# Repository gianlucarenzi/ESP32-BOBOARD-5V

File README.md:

# ESP32-BOBOARD-5V

**ESP32 NodeMCU 5V Tolerant Breakout Board per Monitoraggio Bus 6502**

## 🌐 Language / Lingua

---

## 📋 Indice

- [Panoramica del Progetto](#panoramica-del-progetto)
- [Caratteristiche Principali](#caratteristiche-principali)
- [Specifiche Tecniche](#specifiche-tecniche)
- [Visualizzazione 3D](#visualizzazione-3d)
- [Architettura Hardware](#architettura-hardware)
- [Firmware](#firmware)
- [Installazione e Setup](#installazione-e-setup)
- [Utilizzo](#utilizzo)
- [Diagrammi di Flusso](#diagrammi-di-flusso)
- [Tempistiche](#tempistiche)
- [File del Progetto](#file-del-progetto)
- [Produzione](#produzione)
- [Licenza](#licenza)
- [Contributi](#contributi)

## 🎯 Panoramica del Progetto

ESP32-BOBOARD-5V è una scheda breakout specializzata progettata per interfacciare un modulo ESP32 NodeMCU con sistemi basati su processore 6502, come l'Atari 8-bit. La scheda fornisce:

- **Tolleranza 5V** per tutti i pin GPIO
- **Monitoraggio del bus 6502** in tempo reale
- **Implementazione PBI (Parallel Bus Interface)** per Atari
- **Level shifting bidirezionale** per compatibilità 3.3V/5V
- **Connettori standard** per facile integrazione

### 🎮 Applicazioni Principali

- Monitoraggio e debug di sistemi 6502
- Implementazione di periferiche PBI per Atari
- Analisi del traffico del bus dati/indirizzi
- Espansione RAM a pagine da oltre 200 KB per Atari 130XE, finestra da 256 byte in $D500 (in stile GeoRAM)
- Espansione RAM 256 KB compatibile GeoRAM per Commodore 64, sulla porta di espansione (ambiente `c64`)
- Sviluppo di cartucce intelligenti

## ✨ Caratteristiche Principali

### Hardware
- **ESP32 NodeMCU** compatibile (240MHz dual-core)
- **3x TXS0108E** level shifters bidirezionali
- **Tolleranza 5V** su tutti i pin GPIO
- **Connettore USB-C** per programmazione e alimentazione
- **Connettore PBI** standard per Atari
- **Pin header** per accesso completo ai GPIO
- **LED di stato** e pulsanti di controllo

### Firmware
- **Espansione RAM a pagine da oltre 200 KB per Atari 130XE, in stile GeoRAM, senza ROM**: registri in $D100–$D1FF (`~D1XX`) e finestra RAM in $D500–$D5FF (`~CCTL`), decodificate dalla MMU/PLA dell'Atari; solo A0–A7 campionati
- **Ruoli fissi**: finestra RAM di 256 byte in $D500–$D5FF; registri in $D1xx: numero di banchi a $D1FB–$D1FC (sola lettura), registro del banco a 16 bit a $D1FD–$D1FE, latch di selezione PBI a $D1FF (bit 7, ID dispositivo `$80`); da non selezionato non pilota mai il bus
- **Banchi dall'heap**: all'avvio il firmware prende la DRAM libera dell'ESP32 in banchi da 256 byte (stima 200–230 KB, il valore esatto è stampato all'avvio)
- **Espansione RAM 256 KB compatibile GeoRAM per C64 (ambiente `c64`)**: la stessa scheda sulla porta di espansione: finestra RAM in IO1 $DE00–$DEFF, pagina in $DFFE e blocco da 16 KB in $DFFF (solo scrittura); /IO1 su J3 pin 12, /IO2 su J3 pin 11; 256 KB (16 blocchi, con ripiegamento degli indirizzi come una GeoRAM vera: circa 210 KB dalla DRAM e il resto dall'IRAM dell'ESP32)
- **Nessuna ROM, nessun MPD / EXTSEL**: tutti i pin del bus sono ingressi, D0–D7 diventano uscite solo per rispondere a una lettura
- **Dual-core**: Core 1 dedicato al bus (interrupt mascherati, decodifica durante PHI1), Core 0 stampa il log
- **Log lock-free** (Core 1 → Core 0): ogni accesso alle due pagine e ogni cambio di latch, con timestamp in microsecondi

## 🔧 Specifiche Tecniche

| Parametro | Valore |
|-----------|--------|
| **Microcontrollore** | ESP32-WROOM-32 |
| **Frequenza CPU** | 240 MHz (dual-core) |
| **Memoria Flash** | 4MB |
| **RAM** | 520KB |
| **GPIO disponibili** | 30 pin |
| **Level Shifters** | 3x TXS0108E (8-bit bidirezionali) |
| **Alimentazione** | 5V via USB-C o pin |
| **Logica I/O** | 3.3V/5V tolerant |
| **Dimensioni PCB** | 21.7mm x 21.7mm |
| **Layers** | 4 layer PCB |

### Pinout 6502 Bus

| Segnale | Pin ESP32 | Descrizione |
|---------|-----------|-------------|
| **D0-D7** | GPIO4, GPIO5, GPIO13, GPIO14, GPIO16, GPIO17, GPIO18, GPIO19 | Data Bus (Bidirezionale) |
| **A0-A3** | GPIO34, GPIO35, GPIO36, GPIO39 | Address Bus LSB (Input Only) |
| **A4-A7** | GPIO32, GPIO33, GPIO21, GPIO27 | Address Bus |
| **PHI2** | GPIO2 | Clock 6502 (1.79 MHz) |
| **R/W** | GPIO15 | Read/Write |
| **~D1XX** | GPIO22 | Pagina $D100–$D1FF, dalla MMU/PLA (Active Low, Input) |
| **~CCTL** | GPIO23 | Pagina $D500–$D5FF, dalla MMU/PLA (Active Low, Input) |
| **TX debug** | GPIO1 | Console seriale 115200 bps (anche su J4 pin 3) |

Non usati dal firmware: GPIO12 (ancora collegato a U1 / J3 pin 4, pin di strapping), GPIO25 e GPIO26 (canali TXS0108E liberi), GPIO0 e GPIO3 (non portati su J3).

## 🎨 Visualizzazione 3D

### 📱 Viewer Online Interattivi

Visualizza i modelli 3D direttamente nel browser:

### 📥 Download File 3D

| Formato | Descrizione | Download |
|---------|-------------|----------|
| **STEP** | Modello CAD parametrico |  |
| **WRL** | Modello VRML per rendering |  |

### 🖼️ Galleria Immagini 3D

<table>
  <tr>
    <td align="center">
      
      <br/><b>Vista Isometrica</b>
    </td>
    <td align="center">
      
      <br/><b>Vista Superiore</b>
    </td>
  </tr>
  <tr>
    <td align="center">
      
      <br/><b>Vista Inferiore</b>
    </td>
    <td align="center">
      
      <br/><b><a href="schematics/ESP32-BOBOARD-5V.pdf">📄 Schema Elettrico</a></b>
    </td>
  </tr>
</table>

### 🛠️ Software Consigliati per Visualizzazione

| Software | Formato | Piattaforma | Gratuito |
|----------|---------|-------------|----------|
| **FreeCAD** | STEP, WRL | Windows, Linux, macOS | ✅ |
| **Fusion 360** | STEP | Windows, macOS | ✅ (Personal) |
| **Blender** | WRL | Windows, Linux, macOS | ✅ |
| **MeshLab** | WRL | Windows, Linux, macOS | ✅ |
| **CAD Exchanger Viewer** | STEP, WRL | Browser | ✅ |
| **3D Viewer Online** | STEP, WRL | Browser | ✅ |
| **Autodesk Viewer** | STEP | Browser | ✅ |

---

## 🏗️ Architettura Hardware

### Schema a Blocchi

### Level Shifting

La scheda utilizza tre TXS0108E per garantire la compatibilità tra i livelli logici 3.3V dell'ESP32 e i 5V del sistema 6502.  I canali seguono i pin del modulo, non le funzioni:

- **U1**: PHI2 (GPIO2), D0 (GPIO4), D1 (GPIO5), GPIO12 (non usato), D2 (GPIO13), D3 (GPIO14), R/W (GPIO15), D6 (GPIO18)
- **U3**: D7 (GPIO19), A6 (GPIO21), ~D1XX (GPIO22), ~CCTL (GPIO23), GPIO25 e GPIO26 (liberi), A7 (GPIO27), A4 (GPIO32)
- **U4**: A5 (GPIO33), A0 (GPIO34), A1 (GPIO35), A2 (GPIO36), A3 (GPIO39), D4 (GPIO16), D5 (GPIO17); canale 8 libero

`TXS_EN` (OE di tutti e tre) è tenuto alto da R1/R3/R4; SW1 lo porta a GND per isolare l'ESP32 dal bus.

## 💻 Firmware

### Architettura Software

Il firmware è basato su FreeRTOS e utilizza entrambi i core dell'ESP32:

- **Core 0**: `LogTask`, unico scrittore sulla seriale
- **Core 1**: `MonitorTask` in IRAM, con interrupt mascherati e watchdog degli interrupt disattivato, possiede il bus 6502

### Funzionalità Principali

#### 1. Ciclo di bus

- **PHI1**: 200 ns dopo la discesa di PHI2 (`BUS_ADDR_SETTLE_NS`) campiona A0–A7, R/W, `~D1XX` e `~CCTL`; per una lettura della finestra RAM o di un registro ($D1FB–$D1FE) scrive il byte in `GPIO.out` con le uscite ancora spente
- **Salita di PHI2**: un solo store accende D0–D7; se la selezione compare solo sul fronte di salita, il byte viene pilotato in ritardo
- **Scrittura**: il dato è campionato 120 ns dopo la salita di PHI2 (`BUS_WR_SAMPLE_NS`)
- **Discesa di PHI2**: D0–D7 rilasciati; l'evento del ciclo va nel log durante la PHI1 successiva

#### 2. Atari 130XE: espansione RAM a pagine da oltre 200 KB (in stile GeoRAM)

Non è una GeoRAM (sull'Atari non è mai esistita) e non è compatibile con la memoria estesa del 130XE / RAMBO, quella commutata via PORTB in $4000–$7FFF: DOS con RAMdisk e programmi per la memoria estesa non la vedono, serve software scritto per questa mappa.  La quantità esatta (stima 200–230 KB) la stampa il banner all'avvio.

Ruoli fissi, come la GeoRAM del C64 fra IO2 e IO1: la pagina PBI $D1xx contiene i registri, la pagina CCTL $D500–$D5FF è una finestra di 256 byte sulla RAM.

| Indirizzo | Funzione | Note |
|-----------|----------|------|
| **$D500–$D5FF** | Finestra RAM: 256 byte del banco corrente (R/W) | Solo con il dispositivo selezionato |
| **$D1FB–$D1FC** | Numero di banchi (R, 16 bit) | Dipende dall'heap libero, scritture ignorate |
| **$D1FD–$D1FE** | Registro del banco (R/W, 16 bit, little-endian) | Un banco oltre il numero disponibile non risponde |
| **$D1FF** | Latch di selezione PBI (W: bit 7 = ID `$80`) | Mai pilotato in lettura ($D1FF è lo stato IRQ PBI) |
| **$D100–$D1FA** | Riservato | Mai pilotato, scritture ignorate |

Regole PBI: una scrittura in $D1FF seleziona il dispositivo con il bit 7 a 1 e lo deseleziona con il bit 7 a 0 (ogni dispositivo PBI guarda solo il proprio bit).  Da non selezionato non pilota mai il bus e ignora ogni scrittura tranne il latch.

Collegamento all'Atari 130XE (slot cartuccia ed ECI).  Sull'800XL il connettore PBI non porta `~D1XX`: $D1xx va decodificato da A8–A15 con logica esterna, non prevista su questa scheda:

Vista breadboard, stile Fritzing:

I banchi da 256 byte vengono allocati all'avvio dall'heap DRAM libero dell'ESP32 (meno 24 KB di riserva per il sistema).  Indirizzo lineare: banco = indirizzo >> 8, offset = indirizzo & $FF.  All'accensione: non selezionato, banco 0, RAM a `$00`; il dispositivo non vede il RESET dell'Atari e mantiene lo stato, la RAM non si conserva al reset dell'ESP32.  Senza ROM la scansione PBI dell'OS non trova la firma a $D803 / $D80B e salta il dispositivo: i programmi lo selezionano direttamente scrivendo `$80` in $D1FF; la scansione scrive `$80` e poi `$00` in $D1FF, quindi il dispositivo resta deselezionato.

#### 3. Commodore 64: espansione RAM 256 KB compatibile GeoRAM (ambiente `c64`)

La stessa scheda, con l'ambiente `c64` (`-D BUS_C64=1`), diventa un'espansione RAM compatibile GeoRAM (stessi registri $DE00, $DFFE, $DFFF) per la porta di espansione del C64, con lo stesso schema del firmware di Vera-Module-RBL-C64.  "geoRAM" era un prodotto di Berkeley Softworks, solo nel taglio da 512 KB: questa è un'espansione compatibile da 256 KB, da confermare con il banner all'avvio.

| Indirizzo | Funzione | Note |
|-----------|----------|------|
| **$DE00–$DEFF** (/IO1) | Finestra di 256 byte sulla RAM | Lettura e scrittura |
| **$DFFE** (/IO2) | Pagina nel blocco (0–63) | Solo scrittura, in lettura non pilotato |
| **$DFFF** (/IO2) | Blocco da 16 KB (0–15) | Solo scrittura, in lettura non pilotato |

- **Sempre attiva**, senza latch, come la cartuccia originale; il resto di IO2 non è decodificato (nessun mirror in $DF80–$DFFD)
- **256 KB, 16 blocchi**: indirizzo = blocco × 16384 + pagina × 256 + offset; il blocco è limitato alla dimensione (il blocco 16 coincide con lo 0) come su una GeoRAM vera, così la rilevazione della dimensione vede una 256 KB.  `-D GEORAM_KB=...` per un'altra potenza di 2
- **Memoria**: circa 210 KB dalla DRAM dell'ESP32 e il resto dall'IRAM libera, letta e scritta solo a 32 bit; se non basta, il firmware scende a 128 KB e lo dice nel banner.  La geoRAM originale era da 512 KB: il software che pretende quel taglio non funziona
- **Ciclo di bus**: il VIC-II possiede il bus durante PHI1, quindi tutto avviene con PHI2 alto: dopo la salita il firmware attende /IO1 o /IO2 per al massimo 200 ns (`IO_QUALIFY_NS`), legge A0–A7 e, in lettura, pilota subito il byte fino alla discesa di PHI2; in scrittura il dato è campionato 300 ns dopo la salita (`BUS_WR_SAMPLE_NS`)
- **Stato**: azzerato all'accensione, mantenuto al reset del C64; la RAM non si conserva al reset dell'ESP32

Collegamento alla porta di espansione (pinout del C64 verificato su c64-wiki.com e retroisle.com):

Vista breadboard, stile Fritzing:

| Segnale | Porta C64 | J3 |
|---------|-----------|----|
| **/IO1** | 7 | 12 (GPIO23, ingresso `~CCTL`) |
| **/IO2** | 10 | 11 (GPIO22, ingresso `~D1XX`) |
| D0 / D1 / D2 / D3 | 21 / 20 / 19 / 18 | 2 / 3 / 5 / 6 |
| D4 / D5 / D6 / D7 | 17 / 16 / 15 / 14 | 22 / 23 / 8 / 9 |
| A0 / A1 / A2 / A3 | Y / X / W / V | 18 / 19 / 20 / 21 |
| A4 / A5 / A6 / A7 | U / T / S / R | 16 / 17 / 10 / 15 |
| Φ2 | E | 1 |
| R/W | 5 | 7 |
| GND | 1, 22, A, Z | 29, 30 |
| +5V | 2, 3 | 31, 32 |

Output seriale (i numeri di pagine e di memoria libera dipendono dalla scheda):

```
[6502_monitor] GeoRAM on the C64 expansion port: 256 KB = 16 blocks x 16 KB
[6502_monitor] Pages: <d> in DRAM, <i> in IRAM, <b> heap blocks; left <h> bytes DRAM, <r> bytes IRAM
[6502_monitor] IO1 $DE00-$DEFF RAM, IO2 $DFFE page, $DFFF block (write-only)
[6502_monitor] /IO1 on J3 pin 12 (GPIO23), /IO2 on J3 pin 11 (GPIO22)
[6502_monitor] Bus loop on Core 1 (/IOx within 200 ns, write sample 300 ns after PHI2 rises), log 115200 baud
[    2.000000] [DFFF - GEORAM_BLOCK        ] W $04  SEL
[    2.000010] [DFFE - GEORAM_PAGE         ] W $23  SEL
[    2.000020] [DE45 - RAM blk $04 pg $23 +$45] R $12  SEL DRV
```

Uso dal C64:
```
LDA #$04 : STA $DFFF   ; blocco 4
LDA #$23 : STA $DFFE   ; pagina 35
LDA $DE45              ; byte GeoRAM $12345
```

Da verificare sull'hardware: il banner (256 KB effettivi), le temporizzazioni all'oscilloscopio e la compatibilità con GEOS e il software GeoRAM.

## 🚀 Installazione e Setup

### Requisiti Hardware
- ESP32 NodeMCU DevKit V1 (30 pin, ESP32-WROOM-32)
- Cavo USB-C per programmazione
- Sistema 6502 target (es. Atari 130XE)
- Connessioni bus secondo pinout

### Requisiti Software
- [PlatformIO](https://platformio.org/) o Arduino IDE
- ESP32 Arduino Core v2.0.14
- Driver USB-C per il sistema operativo

### Compilazione Firmware

1. **Clone del repository**:
```bash
git clone https://github.com/gianlucarenzi/esp32-boboard-5v.git
cd ESP32-BOBOARD-5V/firmware/6502_monitor
```

2. **Configurazione PlatformIO** (estratto di `platformio.ini`):
```ini
[env]
extra_scripts = post:efuse_vdd_sdio.py
monitor_rts = 0
monitor_dtr = 0
custom_efuse_vdd_sdio = 3.3V

[env:nodemcu-32s]
platform = espressif32@6.6.0
board = nodemcu-32s
framework = arduino
monitor_speed = 115200
upload_speed = 921600
board_build.f_cpu = 240000000

[env:c64]                      ; Commodore 64, GeoRAM
extends = env:nodemcu-32s
build_flags = ${env:nodemcu-32s.build_flags} -D BUS_C64=1
```

Il modulo si programma **sempre scollegato dall'Atari o dal C64**, collegato solo al PC.  Prima di ogni upload `efuse_vdd_sdio.py` verifica gli efuse VDD_SDIO e, se sono vergini, li programma a 3,3 V (**irreversibile**), così GPIO12 non viene più letto al reset.

3. **Compilazione e upload**:
```bash
pio run -e nodemcu-32s --target upload   # Atari
pio run -e c64 --target upload           # Commodore 64 (GeoRAM)
pio device monitor
```

### Configurazione Hardware

1. **Connessione ESP32**: Inserire il modulo NodeMCU nei socket
2. **Alimentazione**: Collegare USB-C o alimentazione 5V
3. **Bus 6502**: Collegare secondo il pinout specificato
4. **Test**: Eseguire modalità test per verifica connessioni

## 📊 Utilizzo

### Avvio Sistema

1. **Power-on**: Alimentare la scheda
2. **Monitor seriale**: Aprire terminale a 115200 baud
3. **Inizializzazione**: Attendere messaggio di ready
4. **Connessione 6502**: Collegare al sistema target

### Output Seriale

Il firmware stampa su Core 0 ogni evento registrato da Core 1 in un ring buffer lock-free.
Il formato è `[secondi.microsecondi]`:

```
[6502_monitor] Banked RAM PBI / CCTL peripheral, device ID $80
[6502_monitor] <n> banks x 256 bytes = <k> KB, <b> heap blocks, <h> bytes of heap left
[6502_monitor] RAM window $D500-$D5FF; count $D1FB-$D1FC, bank $D1FD-$D1FE, select $D1FF
[6502_monitor] Bus loop on Core 1 (settle 200 ns, write sample 120 ns), log 115200 baud
[    1.234567] [D1FF - PBI_SELECT          ] W $80  SELECTED
[    1.234601] [D1FD - BANK_SELECT_L       ] W $03  SEL
[    1.234620] [D1FE - BANK_SELECT_H       ] W $01  SEL
[    1.234640] [D505 - RAM bank $0103 +$05 ] W $AA  SEL
[    1.234680] [D505 - RAM bank $0103 +$05 ] R $AA  SEL DRV
[    1.300000] [D105 - RESERVED            ] R $FF  SEL
```

- `PBI_SELECT` — scrittura del latch e nuovo stato: `SELECTED` / `DESELECTED`
- `SEL` = dispositivo selezionato, `DRV` = byte pilotato dal dispositivo, `-` = non selezionato (il byte è quello presente sul bus)
- Gli offset sono mostrati come `RAM bank $bbbb +$oo`, `BANK_COUNT_L/H`, `BANK_SELECT_L/H`, `PBI_SELECT` o `RESERVED`; i numeri di banchi nell'esempio sono indicativi
- Il timestamp viene dal contatore di cicli del Core 1 (CCOUNT esteso a 64 bit)
- Ogni riga è una sola `Serial.write()`: le righe non si mescolano mai; gli eventi persi quando il ring è pieno vengono contati
- Debug in sola lettura anche su J4: GND (pin 1) e TX0 (pin 3, 3,3 V); RX0 (pin 2) va lasciato scollegato

## 📈 Diagrammi di Flusso

### Flusso Principale del Monitor

### Protocollo di Selezione (PBI)

## ⏱️ Tempistiche

### Timing Critici

| Operazione | Tempo | Note |
|------------|-------|------|
| **PHI2 Period** | 1.77 MHz (PAL) / 1.79 MHz (NTSC) | Clock Atari 6502 |
| **Address Setup** | <100ns | Prima del rising edge PHI2 |
| **Data Setup** | <200ns | Per operazioni di write |
| **Data Hold** | <100ns | Dopo falling edge PHI2 |
| **GPIO Read** | ~125ns | Lettura registri ESP32 |
| **Level Shift** | <10ns | Propagazione TXS0108E |

### Diagramma Temporale Bus 6502

Ciclo di bus Atari visto dal firmware `nodemcu-32s` (ns dalla discesa di PHI2; generato da [`docs/timing.py`](firmware/6502_monitor/docs/timing.py)):

### Performance del Monitor

- **Campionamento**: un ciclo di bus per volta, Core 1 dedicato al 100%
- **Risposta in lettura**: byte (RAM del banco o registro) preparato durante PHI1, uscite accese subito dopo la salita di PHI2 (da misurare all'oscilloscopio)
- **Throughput seriale**: 115200 baud per debug (`LOG_BAUD`)
- **Compatibilità**: Atari PAL (1.77 MHz) e NTSC (1.79 MHz)

## 📁 File del Progetto

### Struttura Directory

```
ESP32-BOBOARD-5V/
├── 📁 firmware/
│   └── 📁 6502_monitor/
│       ├── 📄 platformio.ini          # Configurazione PlatformIO (ambienti nodemcu-32s / Atari e c64 / C64)
│       ├── 📄 efuse_vdd_sdio.py       # Controllo/programmazione efuse VDD_SDIO prima di ogni upload
│       ├── 📁 src/
│       │   └── 📄 main.cpp            # Firmware ESP32 (RAM a banchi PBI/CCTL + monitor)
│       ├── 📄 README.md, HARDWARE.md, PIN_MAPPING.md/.tex/.pdf, Logs.md
├── 📁 schematics/
│   └── 📄 ESP32-BOBOARD-5V.pdf    # Schema elettrico
├── 📁 3D/
│   ├── 🖼️ ESP32-BOBOARD-5V.png    # Render 3D
│   ├── 🖼️ ESP32-BOBOARD-5V_TOP.png
│   └── 🖼️ ESP32-BOBOARD-5V_BOTTOM.png
├── 📁 images/
│   ├── 📄 ESP32-BOBOARD-5V.step   # Modello 3D (output_job.sh)
│   └── 📄 ESP32-BOBOARD-5V.wrl    # Modello VRML (output_job.sh)
├── 📁 production/
│   ├── 📄 *.gbl, *.gtl           # File Gerber
│   ├── 📄 *.drl                  # File drill
│   └── 📄 ESP32BOBOARD-5V-1.0.zip
├── 📁 ibom/
│   └── 📄 ibom.html              # Interactive BOM
├── 📄 ESP32-BOBOARD-5V.kicad_pcb  # PCB KiCad
├── 📄 ESP32-BOBOARD-5V.sch        # Schema KiCad
├── 📄 ESP32-BOBOARD-5V.csv        # Bill of Materials
└── 📄 README.md                   # Questo file
```

### File di Produzione

#### Bill of Materials (BOM)

| Componente | Quantità | Package | LCSC Part |
|------------|----------|---------|-----------|
| **TXS0108EPW** | 3 | TSSOP-20 | C17206 |
| **100µF Capacitor** | 9 | 0805 | C141660 |
| **100nF Capacitor** | 1 | 0805 | C840116 |
| **10kΩ Resistor** | 4 | 0805 | C84376 |
| **5.1kΩ Resistor** | 2 | 0805 | C27834 |
| **1% Precision Resistor** | 2 | 0805 | C328378 |
| **Pin Socket 1x15** | 2 | THT | - |
| **Pin Header 2x16** | 1 | SMD | C6332241 |
| **USB-C Connector** | 1 | SMD | C3197885 |
| **SPST Switch** | 1 | SMD | C319052 |

#### File Gerber
- **4-layer PCB** ottimizzato per segnali ad alta velocità
- **Impedenza controllata** per linee critiche
- **Ground planes** per riduzione EMI
- **Via stitching** per integrità del segnale

## 🏭 Produzione

### Specifiche PCB

| Parametro | Valore |
|-----------|--------|
| **Layers** | 4 |
| **Thickness** | 1.6mm |
| **Min Track** | 0.1mm |
| **Min Via** | 0.2mm |
| **Copper Weight** | 1oz (35μm) |
| **Surface Finish** | HASL Lead-Free |
| **Solder Mask** | Green |
| **Silkscreen** | White |

### Assembly

1. **SMD Components**: Assemblaggio automatico raccomandato
2. **THT Components**: Saldatura manuale pin headers
3. **Test**: Verifica continuità e test funzionale
4. **Programming**: Upload firmware di test

## 📜 Licenza

Questo progetto è rilasciato sotto **GNU General Public License v3.0**.

```
ESP32-BOBOARD-5V - ESP32 NodeMCU 5V Tolerant Breakout Board
Copyright (C) 2024 RetroBitLab

This program is free software: you can redistribute it and/or modify
it under the terms of the GNU General Public License as published by
the Free Software Foundation, either version 3 of the License, or
(at your option) any later version.
```

Vedi il file [LICENSE](LICENSE) per i dettagli completi.

## 🤝 Contributi

I contributi sono benvenuti! Per contribuire:

1. **Fork** del repository
2. **Crea** un branch per la tua feature (`git checkout -b feature/AmazingFeature`)
3. **Commit** delle modifiche (`git commit -m 'Add some AmazingFeature'`)
4. **Push** al branch (`git push origin feature/AmazingFeature`)
5. **Apri** una Pull Request

### Aree di Contributo

- 🐛 **Bug fixes** e miglioramenti firmware
- 📚 **Documentazione** e tutorial
- 🔧 **Hardware** ottimizzazioni e varianti
- 🧪 **Testing** e validazione
- 🎨 **Examples** e progetti dimostrativi

### Reporting Issues

Per segnalare problemi, utilizzare il sistema di [Issues](../../issues) includendo:
- Descrizione dettagliata del problema
- Versione hardware e firmware
- Log seriali se disponibili
- Passi per riprodurre il problema

---

## 📞 Contatti

- **Progetto**: ESP32-BOBOARD-5V
- **Autore**: RetroBitLab
Repository: [GitHub](https://github.com/gianlucarenzi/esp32-boboard-5v)
- **Documentazione**: [Wiki](../../wiki)

---

*Realizzato con ❤️ per la comunità retro-computing*

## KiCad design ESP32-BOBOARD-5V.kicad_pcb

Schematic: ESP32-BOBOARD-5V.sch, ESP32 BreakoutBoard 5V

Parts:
C1, C2, C3, C4, C5, C6, C7, C8, C9: 100uF; C_0805_2012Metric_Pad1.18x1.45mm_HandSolder; LCSC C141660
C10: 100nF; C_0805_2012Metric_Pad1.18x1.45mm_HandSolder; LCSC C840116
GR1: LOGO; KiCad-Logo2_5mm_SilkScreen
GR2: LOGO; ESP32_BOBOARD_5V_21.7mmx21.7mm
J1, J2: Conn_01x15; PinSocket_1x15_P2.54mm_Vertical
J3: CONN_02x16_PIN_SMD_Odd_Even_2.54mm; PinHeader_2x16_P2.54mm_Vertical_SMD; LCSC C6332241
J4: Conn_01x03_Male; PinHeader_1x03_P2.54mm_Vertical_SMD_Pin1Left; LCSC C41417360
J5: DX07S016JA1R1500; JAE_DX07S016JA1R1500; PARTREV 1; LCSC C3197885
R1, R2, R3, R4: 10K; R_0805_2012Metric_Pad1.20x1.40mm_HandSolder; LCSC C84376
R5, R6: 5K1; R_0805_2012Metric_Pad1.20x1.40mm_HandSolder; LCSC C27834
R7, R8: CREZ08051%; R_0805_2012Metric_Pad1.20x1.40mm_HandSolder; LCSC C328378
SW1: SPST_SWITCH_SMD_4P,4.1x5.4mm; SW_DIP_SPSTx02_DSHP02TS-S; LCSC C319052
U1, U3, U4: TXS0108EPW; TSSOP-20_4.4x6.5mm_P0.65mm; LCSC C17206

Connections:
+3V3: C1.1, C4.1, C6.1, C8.1, J1.1, J3.27, J3.28, R1.2, R2.2, R3.2, R4.2, U1.2 (VCCA), U3.2 (VCCA), U4.2 (VCCA)
+5V: C2.1, C3.1, C5.1, C7.1, C9.1, J2.1, J3.31, J3.32, J5.2 (VBUS), J5.11 (VBUS), U1.19 (VCCB), U3.19 (VCCB), U4.19 (VCCB)
/D2: J1.4, U1.1 (A1)
/D4: J1.5, U1.3 (A2)
/D5: J1.8, U1.4 (A3)
/D12: J2.4, U1.5 (A4)
/D13: J2.3, U1.6 (A5)
/D14: J2.5, U1.7 (A6)
/D15: J1.3, U1.8 (A7)
/D18: J1.9, U1.9 (A8)
/D19: J1.10, U3.1 (A1)
/D21: J1.11, U3.3 (A2)
/D22: J1.14, U3.4 (A3)
/D23: J1.15, U3.5 (A4)
/D25: J2.8, U3.6 (A5)
/D26: J2.7, U3.7 (A6)
/D27: J2.6, U3.8 (A7)
/D32: J2.10, U3.9 (A8)
/D33: J2.9, U4.1 (A1)
/D34: J2.12, U4.3 (A2)
/D35: J2.11, U4.4 (A3)
/EN: J2.15, J3.26, R2.1
/RX0: J1.12, J4.2
/RX2: J1.6, U4.7 (A6)
/TX0: J1.13, J4.3
/TX2: J1.7, U4.8 (A7)
/USBD_N: J5.5 (D-), J5.8 (D-), R7.1
/USBD_P: J5.6 (D+), J5.7 (D+), R8.1
/VN: J2.13, U4.6 (A5)
/VP: J2.14, U4.5 (A4)
/mD2: J3.1, U1.20 (B1)
/mD4: J3.2, U1.18 (B2)
/mD5: J3.3, U1.17 (B3)
/mD12: J3.4, U1.16 (B4)
/mD13: J3.5, U1.15 (B5)
/mD14: J3.6, U1.14 (B6)
/mD15: J3.7, U1.13 (B7)
/mD18: J3.8, U1.12 (B8)
/mD19: J3.9, U3.20 (B1)
/mD21: J3.10, U3.18 (B2)
/mD22: J3.11, U3.17 (B3)
/mD23: J3.12, U3.16 (B4)
/mD25: J3.13, U3.15 (B5)
/mD26: J3.14, U3.14 (B6)
/mD27: J3.15, U3.13 (B7)
/mD32: J3.16, U3.12 (B8)
/mD33: J3.17, U4.20 (B1)
/mD34: J3.18, U4.18 (B2)
/mD35: J3.19, U4.17 (B3)
/mRX2: J3.22, U4.14 (B6)
/mTX2: J3.23, U4.13 (B7)
/mVN: J3.21, U4.15 (B5)
/mVP: J3.20, U4.16 (B4)
GND: C1.2, C2.2, C3.2, C4.2, C5.2, C6.2, C7.2, C8.2, C9.2, C10.2, J1.2, J2.2, J3.29, J3.30, J4.1, J5.1 (GND), J5.12 (GND), R5.2, R6.1, SW1.2, U1.11 (GND), U3.11 (GND), U4.11 (GND)
unnamed: C10.1, J5.S1 (SHIELD), J5.S2 (SHIELD), J5.S3 (SHIELD), J5.S4 (SHIELD), J5.S5 (SHIELD), J5.S6 (SHIELD)
unnamed: J5.3 (CC1), R5.1
unnamed: J5.9 (CC2), R6.2
TXS_EN: R1.1, R3.1, R4.1, SW1.3, U1.10 (OE), U3.10 (OE), U4.10 (OE)

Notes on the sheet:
Yellow
Orange
Black
DEBUG UART TX0/RX0
ESP32 MODULE STRIP
LEVEL SHIFTERS
5V TOLERANT HEADER CONNECTOR
USB-C POWER
Do not connect USB ESP32 __and__ USB J5 at the same time!
Normal Mode OFF-OFF When PROGRAMMING ESP32 ON-ON

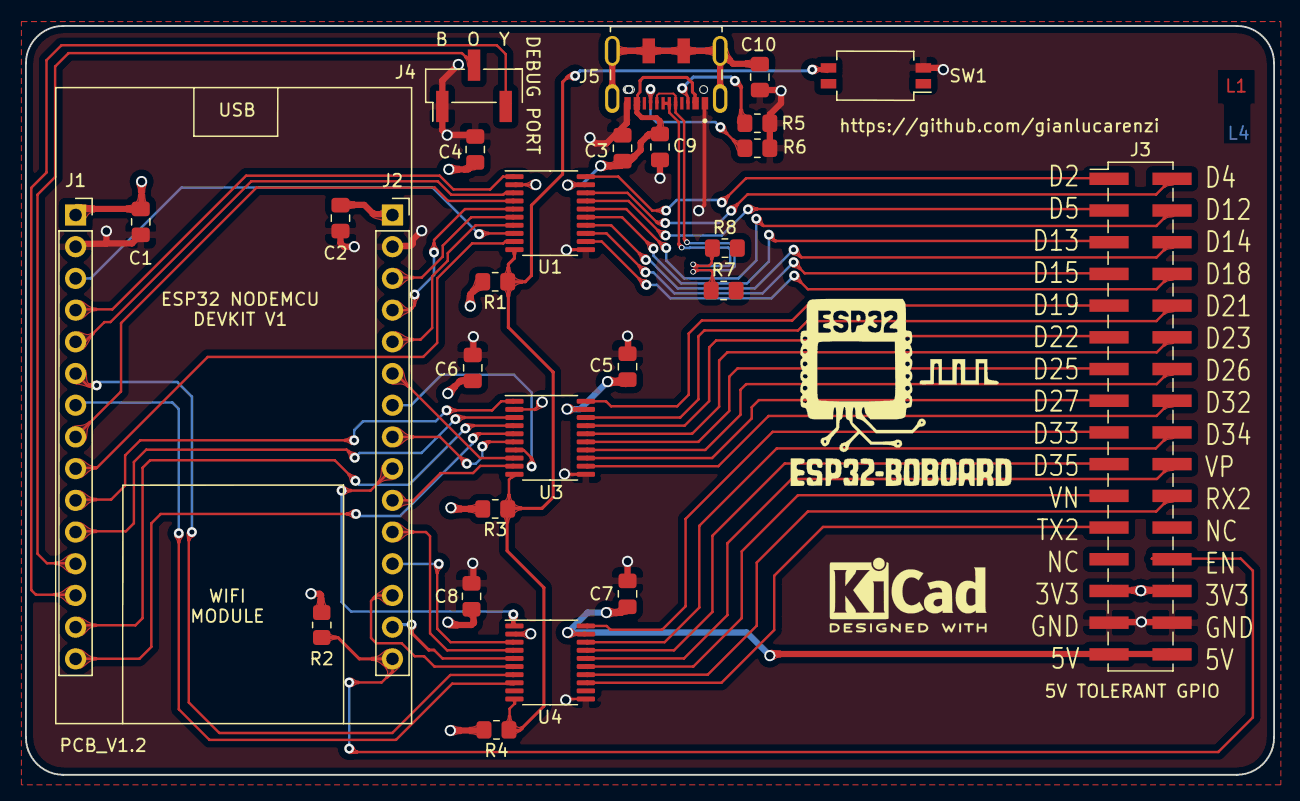
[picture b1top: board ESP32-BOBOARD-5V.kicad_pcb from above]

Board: 4 copper layers, 100.0 x 60.0 mm, 29 parts (0 on the bottom side), 58 nets.

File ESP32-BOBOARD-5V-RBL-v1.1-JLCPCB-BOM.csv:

Comment,Designator,Footprint,LCSC
100nF,C10,Capacitor_SMD:C_1210_3225Metric_Pad1.33x2.70mm_HandSolder,C2351189
100uF,"C1,C2,C3,C4,C5,C6,C7,C8,C9",Capacitor_SMD:C_1210_3225Metric_Pad1.33x2.70mm_HandSolder,C90143
Conn_02x16_Counter_Clockwise,J3,Connector_PinHeader_2.54mm:PinHeader_2x16_P2.54mm_Vertical_SMD,C3294474 
Conn_01x03_Male,J4,Connector_PinHeader_2.54mm:PinHeader_1x03_P2.54mm_Vertical_SMD_Pin1Left,C41417360
DX07S016JA1R1500,J5,RetroBitLab:JAE_DX07S016JA1R1500,C3197885
10K,"R1,R2,R3,R4",Resistor_SMD:R_1210_3225Metric_Pad1.30x2.65mm_HandSolder,C620660
5K1,"R5,R6",Resistor_SMD:R_1210_3225Metric_Pad1.30x2.65mm_HandSolder,C2119494
CREZ12101%,"R7,R8",Resistor_SMD:R_1210_3225Metric_Pad1.30x2.65mm_HandSolder,C2974058
"SPST_SWITCH_SMD_4P,4.1x5.4mm",SW1,RetroBitLab:SW_DIP_SPSTx02_DSHP02TS-S,C319052
TXS0108EPW,"U1,U3,U4",Package_SO:TSSOP-20_4.4x6.5mm_P0.65mm,C17206

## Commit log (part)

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2025-07-23 Added via UPLOAD
2025-07-23 Sent to JLCPCB 23 Jul 2025 PCB V1.0
2025-07-23 First plot
2025-07-23 First build
2025-07-23 First 3D
2025-07-23 Updated with area-fills and other silkscreen information
2025-07-31 First commit. Compile in a shell
2025-07-31 Settings for UART
2025-07-31 First commit.
2025-07-31 GPIO Manual Test
2025-07-31 AUTO TEST (Shorting IN <--> OUT)
2025-07-31 Normal mode by default
2025-07-31 Aggiornato commento. Attenzione: il pin 36 non viene testato
2025-08-01 Not useful. Must be in the .gitignore
2025-08-01 Added the dip-switch for programming
2025-08-01 Added the dip-switch for programming Added the ESP32 BOBOARD LOGO
2025-08-01 The Montor code is now on CPU Core 1 (it's seems to be quicker than Core 0) Core 0 is now running SerialTask
2025-09-12 Template/Placeholder
2025-09-15 Updated to a better execution timeslice
2025-09-19 Added to project. Must be checked first!
2025-09-19 Updated to reflect new components from library and LCSC availability
2025-09-19 Added
2025-09-19 UUpdated to reflect new components from library and LCSC availability
2025-09-19 Removed. Now we use the automatic configurator
2025-09-19 removed
2025-09-19 From 1210 to 0805 as the first are pretty hard to find nowadays.
2025-09-19 ignored the bak file
2025-09-19 No BOTTOM components
2025-09-22 Shadow RAM @$D6XX is 256bytes only. @$D7XX returns $EA (NOP)
2025-09-23 Better README.md
2025-09-23 Updated/Typos
2025-09-23 English version
2025-09-23 Updated for 3D / Images
2025-10-08 More optimizations
2025-10-08 ANSI Color update
2025-10-30 Update scripts
2025-10-30 Autogeneration tools
2025-10-30 Regenerated
2025-10-30 Autogeneration tools EEPLOT
2025-10-30 Ignored compiled tools
2025-10-30 Opened/Closed for Plotting
2026-05-05 Optimization. The pinout must be defined!
2026-05-05 Mapping for Atari Computers
2026-05-05 Optimization layout
2026-05-05 Corrected pin mapping with the latest version
2026-05-05 After an update this is mandatory
2026-05-05 datasheet
2026-05-06 High speed implementation of decoding logic for a PBI Device on Atari XE
2026-05-06 First try for SID Board (ESP32 emulated)
2026-05-06 just compiled in
2026-05-06 ignored partial pbi artifacts
2026-05-06 added examples
2026-05-06 Updated to emulate SID and its 32 registers. Now the SID Emulator can be used as a standard I/O IOCB Device
2026-05-06 Updated. Now every PUT or GET can be used as ADDR REG & DATA registers as IOCB
2026-05-06 updated for VERA Test
2026-05-08 Added IRAM_ATTR to have this driver in IRAM instead of Flash. Access time for READ/WRITE will be a lot quicker
2026-05-08 Heavily optimized
2026-05-08 Added HW REF
2026-05-08 Updated as in atari800 emulator
2026-05-08 Typo and missing includes
2026-05-08 Ignored because the final code will be in ../include directory
2026-05-08 Updated for Open Drain Configuration
2026-05-08 Added FULL Atari Font to Driver VERA
2026-06-08 feat(6502_monitor): implement dual-mode bus monitor with optimized safe pinout
    - Implemented PBI (, , ) and CCTL () bus modes.
    - Added direct register access and IRAM-resident monitoring for 1.79 MHz compatibility.
    - Designed 'Safe Boot' pinout avoiding GPIO 0 and 12 bootstrap issues.
    - Reconfigured RX0 (GPIO 3) as EXTSEL output while keeping TX0 for debug.
    - Added detailed hardware documentation in Markdown and LaTeX.
2026-06-08 docs: document PBI vs CCTL bus modes and add CCTL build environment
2026-06-08 New pinout for PICO-D4
2026-06-08 Updated for new pin mappings
2026-06-08 build: add PICO-D4 build environments for PBI and CCTL modes
2026-06-12 build: remove ESP32-PICO-D4 support, target NodeMCU DevKit V1 only
    Drop PICO-D4 build environments, pin definitions, conditional branches,
    and mapping documents. Firmware now targets exclusively ESP32-WROOM
    on NodeMCU DevKit V1.
2026-06-12 docs: update main READMEs with correct NodeMCU pinout and bus modes
    Fix outdated GPIO table (was referencing wrong pins), replace the
    old TEST/MONITOR mode section with the actual BUS_MODE_PBI/CCTL
    build flag interface, and remove the stale Control Signals table.
2026-06-12 refactor: simplify to PBI ROM emulator, drop RESET/VCS/RAM emulation
    Remove Atari RESET control, VCS output, RAMSEL and the 512-byte
    emulated RAM. The firmware now only handles:
    - ROMSEL: asserts MPD low and drives pbi_rom[A0-A7] on 6502 reads
    - EXTSEL: asserted on D1XX access when the internal latch is active
    - Latch: set/cleared via D1FF write (PBI), always on (CCTL)
2026-06-12 docs: update READMEs and pin mapping to match simplified firmware
    Remove RAMSEL, VCS, RESET from all pin tables. Simplify firmware
    section to describe the PBI ROM emulator. Regenerate PIN_MAPPING.pdf.
2026-06-12 feat: add A8-A10 for full 2KB PBI ROM decode (no aliasing)
    Wire GPIO 12/25/26 (freed from RESET/VCS/RAMSEL) to A8/A9/A10.
    Expand pbi_rom to 2048 bytes, decode_addr now returns 11-bit address.
    Update all pin mapping docs and regenerate PDF.
2026-06-12 build: auto-assemble PBI handler before every pio build
    Add pre_build.py extra_script: runs make -C 6502/ before linking
    the ESP32 firmware so pbi-driver.h is always up to date.
    Add 'rebuild' target to 6502/Makefile for forced manual recompile.
2026-06-12 build: fix pre-build hook to run before source compilation
    Run make in script body (load time) instead of AddPreAction
    so pbi-driver.h is assembled before any .cpp is compiled.
2026-06-12 build: switch PBI handler source to vera_pbi_handler.s
    Output remains pbi-driver.h for ESP32 firmware compatibility.
2026-06-12 feat: add vera_pbi_handler.s and vera_common.inc 6502 sources
2026-06-12 docs: document vera_pbi_handler.s and 6502 ROM build pipeline
2026-06-12 feat: add FreeRTOS log queue with microsecond timestamps
    Add a 64-entry FreeRTOS queue between Core 1 (MonitorTask) and
    Core 0 (loop) to log PBI bus activity without blocking the bus handler.
    - EVT_LATCH: logged on VCS latch state changes ($D1FF writes that
    flip the latch), carrying new state and data byte
    - EVT_REG: logged on every $D100-$D1FE read or write, carrying
    register offset, data, and direction
2026-06-12 docs: update README to reflect current firmware state
    Remove stale RAM emulation and A8-mirroring sections; add VERA register
    logging with FreeRTOS queue and microsecond timestamps, 6502 ROM build
    pipeline (vera_pbi_handler.s / vera_common.inc / pre_build.py), and
    platformio.ini environment table with pio run commands.
2026-06-12 feat: log VERA register names with DCSEL-aware resolution
    Add vera_reg_name() lookup table in loop() (Core 0) covering all
    named registers from vera_common.inc: ADDR_L/M/H, DATA0/1, CTRL,
    IEN, ISR, muxed DC/FX registers ($09-$0C resolved by shadowing the
    last VERA_CTRL write), and L1 layer registers ($14-$1A).
    Serial output now shows: [D103 - VERA_DATA0 ] R $FF
    Update README serial-output example accordingly.
2026-06-12 docs: align all documentation with current firmware state
    HARDWARE.md: remove stale RAM-at-$D600-$D7FF emulation bullet; fix
    DEV_SEL_N -> SEL_N; restate overview around VERA logging and EXTSEL/MPD.
    Logs.md: add 2026-06-12 entry documenting FreeRTOS log queue with µs
    timestamps, VERA register name resolution (vera_reg_name + DCSEL shadow),
    and the 6502 ROM source restructure (vera_pbi_handler.s / vera_common.inc
    / pre_build.py / platformio.ini dual environments).
2026-06-12 docs: complete Logs.md 2026-06-12 with missing architectural changes
    Add three subsections that were not yet documented:
    - Firmware Simplification: drop RESET/VCS/RAMSEL/512-byte RAM (b58b0f6)
    - Full 2 KB ROM Decode: A8-A10 wired on freed GPIOs 12/25/26 (75b3f3e)
    - NodeMCU-only target: remove ESP32-PICO-D4 environment (8395e40)
2026-06-12 feat: log MPD and EXTSEL state on each bus event
    Aggiunge i bit 2 (MPD) e 3 (EXTSEL) al campo flags di LogEvt,
    derivati dai valori già campionati (lo, latch_active) nei call site
    della MonitorTask — senza letture GPIO aggiuntive in log_send().
    Il log mostra ora MPD=LO/HI e EXTSEL=LO/HI per ogni accesso.
2026-06-12 refactor: unify 6502_monitor pin mapping, CCTL-only mode, DAC1 audio restored
    - Adopt pin mapping from 6502_monitor: data bus on GPIO 4/5/13/14/16/17/18/19,
    A0-A4 on GPIO 34/35/36/39/32, SEL_N on GPIO 22.
    - Remove ROMSEL, MPD, EXTSEL: no ROM served, no PBI output signals.
    - Remove A5-A10: only 5 address bits needed for 32 SID registers.
    - SEL_N now connected to CCTL ($D5xx range).
    - Latch control at offset 0x1F ($D5FF decoded with A0-A4 all high).
2026-06-12 docs: add PIN_MAPPING.md with ESP32/Atari bus signal assignments
2026-06-12 docs: rewrite README for CCTL/SID mode with updated pin mapping and memory map
2026-06-12 fix(csidlight): correct pitch, amplitude and oscillator phase continuity
    - SID_ACTUAL_RATE (22222 Hz) replaces SID_SAMPLE_RATE in _phaseIncFor()
    to match the real esp_timer period (45 µs, not 45.351 µs), eliminating
    the 0.78% sharp pitch error caused by integer truncation in SID_TIMER_US.
    - _masterVol() now multiplies before dividing (nibble*128/48) giving
    voiceVol up to 40 instead of 30, recovering ~33% of lost DAC amplitude.
    - _phase[] advances unconditionally in _tick(); only the mix contribution
2026-06-12 fix: drain log queue one entry per loop() to avoid starving process()
    Serial.printf() at 115200 baud blocks ~3.5 ms per line; draining all 64
    entries in a tight while loop could stall process() for ~220 ms, delaying
    SID register propagation to the audio engine. Switching to a single if
    bounds serial overhead to one line per loop iteration while process() runs
    at full loop rate and the queue drains gradually via its 64-entry buffer.
2026-06-12 docs: update README with cSIDLight fixes and log drain rationale
    Document SID_ACTUAL_RATE (22222 Hz vs nominal 22050 Hz), unconditional
    phase advance in _tick(), corrected master volume formula (multiply before
    divide, max voiceVol 40 per voice), and the one-entry-per-loop log drain
    policy that prevents process() starvation during serial output.
2026-06-12 feat: AUDIO_DEMO mode — Commando SID register replay at 50 Hz
    New build environment nodemcu-32s-demo (-D AUDIO_DEMO) plays back
    Commando_dmp.h (27500 bytes, 1100 frames x 25 SID registers) via a
    dedicated esp_timer at 50 Hz (PAL VBlank rate). demo_tick() writes
    registers 0x00-0x18 to cSIDLight each frame and loops automatically.
    Commando_dmp.h: changed array type char->uint8_t and converted all
    negative initializer values to their unsigned equivalents (v+256) to
2026-06-12 docs: document AUDIO_DEMO build environment and SID register dump format
2026-06-29 fix(6502): set fillval=$FF in linker script; fix main.cpp CCTL comment, PBI ROM init, vera_reg_name
    - pbi-driver.ld: add fillval=$FF so padding matches EPROM-erased value
    - Regenerate pbi-driver.{bin,h} with correct fill
    - main.cpp: add #include pbi-driver.h; init pbi_rom via memcpy from pbi_driver[];
    fix CCTL header comment (same latch mechanism as PBI, address $D5FF not $D1FF);
    add VERA_IRQLINE_L ($08) and Layer 0 registers ($0D-$13) to vera_reg_name()
